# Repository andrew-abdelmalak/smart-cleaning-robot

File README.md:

# Smart Cleaning Robot

MicroPython firmware for a low-cost floor-cleaning robot built on a Raspberry Pi Pico W, with Bluetooth Low Energy (BLE) remote control, ultrasonic obstacle avoidance, and feed-forward plus PID wheel control. It was my bachelor thesis project at the German University in Cairo (GUC), 2025.

<p align="center">
  
  &nbsp;
  
</p>

The robot is a 35 cm round chassis that I designed in SolidWorks and 3D-printed, with a custom KiCad PCB and a repurposed PS3 fan for suction. In autonomous mode it drives straight until something is closer than 15 cm, then pivots left and carries on. From a phone you can drive it, toggle the fan, and sound a horn. The parts cost 3,950 EGP in 2025, about 80 USD at the time.

**[Try it in your browser](https://andrew-abdelmalak.github.io/smart-cleaning-robot/):** the project site runs this firmware, unchanged, in a drawn room you can drive it around, next to the real footage and the build story.

*The project in 34 seconds; select it for the version with sound. Music: “Happy Beats & Business Moves Vol. 10” by Sascha Ende ([ende.app](https://ende.app/en)), [CC BY 4.0](https://creativecommons.org/licenses/by/4.0/).*

## Results

From the prototype tests in the [thesis](https://andrew-abdelmalak.github.io/smart-cleaning-robot/pdfjs/web/viewer.html?file=../../thesis.pdf#page=1) (Table 4.2 and section 5.1.1):

| Metric | Result |
|---|---|
| Battery runtime | More than 60 minutes of continuous autonomous operation |
| BLE range | Stable indoor connection at more than 5 m |
| Straight-line driving | PID correction noticeably reduced drift compared with open loop |
| Stall recovery | Detected a stuck wheel and recovered in simulated stuck conditions |
| Cleaning | Collected light debris (paper, dust) from hard floors |
| System power | About 26 W at 12 V (estimate from component ratings) |
| Build cost | 3,950 EGP in parts (about 80 USD at the June 2025 exchange rate), against 100 to 900 USD for the commercial robots I compared |
| Size and weight | 35 cm diameter, 17 cm high, 2.65 kg |

## How it works

<picture>
  <source media="(prefers-color-scheme: dark)" srcset="docs/diagrams/architecture-dark.svg">
  
</picture>

The firmware is one file, [`firmware/main.py`](firmware/main.py), that runs a 20 ms control loop. Each pass handles, in priority order:

| Priority | Condition | Action |
|---|---|---|
| 1 | Horn on | Buzz the motors at 10% duty as an audible horn |
| 2 | Manual command active | Drive forward, backward, or pivot |
| 3 | Autonomous mode on | Advance the cleaning state machine one step |
| 4 | Otherwise | Make sure both motors are stopped |

### Autonomous cleaning

<picture>
  <source media="(prefers-color-scheme: dark)" srcset="docs/diagrams/state-machine-dark.svg">
  
</picture>

From IDLE, `CLEAN` starts forward driving. An obstacle closer than 15 cm triggers a 39-pulse left pivot. A wheel stall longer than 800 ms triggers a reverse, then the same pivot. Both return to forward driving.

### Motion control

A pure PID controller on the wheel encoders drew enough current to cause brownouts that stalled a motor. The final design uses a feed-forward motor model for most of the drive and keeps the PID only as a small correction to each wheel's target speed. The earlier versions on the way here, from timed driving to per-wheel PID and the tuner that found the final gains, are in [`docs/history/`](docs/history/).

<picture>
  <source media="(prefers-color-scheme: dark)" srcset="docs/diagrams/control-loop-dark.svg">
  
</picture>

| Loop | Purpose | P / I / D |
|---|---|---|
| Straight | Keep both wheels at the same distance travelled | 0.8 / 0.15 / 0.25 |
| Turn progress | Reach the target pivot of 39 encoder pulses | 0.6 / 0.1 / 0.2 |
| Turn balance | Share the pivot between both wheels | 1.5 / 0.05 / 0.3 |

The feed-forward model is `PWM = kS + kV × speed`, fitted per wheel (left: kS 27, kV 0.66; right: kS 30, kV 0.61), with a right-wheel trim of 0.75 and duty capped at 95%. All integrals are clamped to ±15.

## Hardware

| Part | Component | Pins (GP = Pico GPIO) |
|---|---|---|
| Controller | Raspberry Pi Pico W | |
| Motor driver | L298N dual H-bridge | ENA 6, ENB 7, IN1 to IN4 12 to 15 |
| Drive | 2 TT DC gear motors, 66 mm wheels | |
| Wheel encoders | 20-slot optical discs, one channel per wheel | Left 21, right 20 |
| Obstacle sensor | HC-SR04 ultrasonic | TRIG 10, ECHO 11 |
| Suction | PS3 Slim fan, 12 V, on/off through its PWM wire | 8 |
| Status LED | Green LED | 18 |
| Button | Push button to GND, internal pull-up | 16 |
| Power | 12 V Li-ion pack, LM2596S buck converter to 5 V | |
| Chassis and PCB | 3D-printed PLA+, custom KiCad PCB | |

The KiCad project for the board, the SolidWorks files for the printed parts, and their drawings are in [`hardware/`](hardware/). The thesis has the full bill of materials (Appendix A).

## Getting started

You need a Raspberry Pi Pico W with [MicroPython for the Pico W](https://micropython.org/download/RPI_PICO_W/) (the robot ran v1.25.0, from April 2025), [`mpremote`](https://docs.micropython.org/en/latest/reference/mpremote.html), and a phone with [nRF Toolbox](https://www.nordicsemi.com/Products/Development-tools/nrf-toolbox) or another BLE UART app.

1. Flash MicroPython: hold BOOTSEL while you connect USB, then copy the `.uf2` file to the drive that appears.
2. Copy the firmware to the board as `main.py`, so it runs at boot:

   ```bash
   mpremote cp firmware/main.py :main.py
   ```

3. Reset the board. It advertises as `PicoRobot-XXXX`, where `XXXX` comes from the board ID.
4. Connect from nRF Toolbox (UART) and send the commands below.

> [!WARNING]
> Test with the wheels off the ground first, and check the motor wiring before you enable autonomous mode. I tuned the gains and thresholds for this chassis; expect to retune `OBSTACLE_THRESHOLD_CM`, `TURN_PULSES`, and the PID gains for another build.

### Commands

Send these as text over the Nordic UART Service (writes go to RX characteristic `6E400002-B5A3-F393-E0A9-E50E24DCCA9E`). Case and surrounding spaces are ignored.

| Command | Effect |
|---|---|
| `FORWARD` | Drive straight with PID correction. Stops with the horn if an obstacle is closer than 15 cm |
| `BACKWARD`, `LEFT`, `RIGHT` | Drive backward, or pivot in place |
| Same command again | Brake and stop |
| `CLEAN` | From a full stop: toggle autonomous cleaning (fan on, state machine running). While moving: emergency stop |
| `FAN` | Toggle the suction fan (only while stopped) |
| `HORN` | Toggle the horn. Also silences the obstacle alarm |

The push button does the same as `CLEAN`. Losing the BLE connection stops the robot.

| Status LED | Meaning |
|---|---|
| Off | Idle, no phone connected |
| Slow flash | Phone connected |
| Solid | Autonomous cleaning |
| Rapid flash | Horn on or path blocked |

## Development

The tests run the real firmware on your computer against fake `machine`, `bluetooth`, and `time` modules, with a simulated clock that wraps like MicroPython's. They cover the motion math, the command handling, the safety stops, and the state machine. You need [uv](https://docs.astral.sh/uv/).

```bash
uv sync
uv run pytest
uv run ruff check .
uv run ruff format --check .
uv run mpy-cross -o main.mpy firmware/main.py
```

CI runs the same steps on every push and pull request.

The site serves its third-party browser code (MicroPython WebAssembly, transformers.js, and the ONNX runtime) itself. `package.json` lists the versions; nothing installs them. `scripts/vendor.json` pins each file by SHA-256, taken from the npm package tarball after checking the tarball against the registry. Dependabot proposes new versions in `package.json`, and CI then fails until the pins are refreshed on that branch:

```bash
python3 scripts/fetch_vendor.py --update
```

To preview the site locally, fetch the files into `site/vendor/` (ignored by git) and serve `site/`:

```bash
python3 scripts/fetch_vendor.py site/vendor
```

The Pages build also adds Mozilla's PDF.js viewer, pinned by version and SHA-256 in `.github/workflows/pages.yml`, so the thesis links open only on the deployed site.

The site's "Ask the thesis" search ranks passages from `site/thesis-index.json`. `scripts/thesis_latex.py` reads the passages from the thesis LaTeX, so results keep their headings, lists, tables, bold text, and subscripts. The build then places each passage on its PDF page and checks its words and numbers against the PDF's own text, so a parsing mistake stops the build. To rebuild the index after the thesis changes, install poppler's `pdftotext` and run:

```bash
uv sync --group search
uv run scripts/build_thesis_index.py
uv run pytest tests/test_thesis_index.py
```

With the `search` group installed, the tests also embed 21 sample questions and check that most find the section that answers them in the top three results. When I built the index, 17 of the 21 did. CI skips that check because it needs a 23 MB model download, but still checks that the index matches what the parser reads from the LaTeX.

```text
firmware/main.py      MicroPython firmware (copy to the board as main.py)
hardware/             KiCad board, SolidWorks parts, and drawings
scripts/              Builds the thesis search index; fetches the site's pinned libraries
tests/                Host-side tests and hardware fakes
docs/diagrams/        Diagrams used in this README
docs/history/         Earlier firmware versions, kept as written
docs/media/           Demo clips from the thesis presentation and the project video
docs/thesis/          Thesis PDF and its LaTeX source
site/                 Project site: the firmware in a drawn room, and thesis search
```

## Known limitations

These come from the hardware and the hand tuning, and need the robot to fix and verify:

- Navigation is reactive. The robot pivots left at every obstacle; it does not map the room or follow a coverage pattern.
- The turn-balance PID adds the two wheel counts rather than comparing them, because the single-channel encoders cannot tell direction. I tuned the gains with it working that way on the prototype.
- A disconnected ultrasonic sensor reads as a clear path. A missing echo returns 999 cm.
- Pivots have no timeout. A dead encoder during a turn keeps the robot spinning.
- Braking always pulses backward, whatever the direction of travel.
- BLE has no pairing, so any phone in range can connect and drive the robot.
- Cleaning: no check valve and no brushes, so debris can spill and embedded dirt stays.

## Thesis

*Design and Implementation of a Smart Cleaning Robot*, Andrew Khalil Samuel Abdelmalak, Faculty of Engineering and Materials Sciences, German University in Cairo, June 2025.

- [Thesis PDF](https://andrew-abdelmalak.github.io/smart-cleaning-robot/pdfjs/web/viewer.html?file=../../thesis.pdf#page=1)
- [LaTeX source](docs/thesis/main.tex), also on [Overleaf (read only)](https://www.overleaf.com/read/hzhdgbtyqgmt#95d41f)
- [Ask the thesis](https://andrew-abdelmalak.github.io/smart-cleaning-robot/#thesis): semantic search over the thesis on the project site, which links each result to its page in the PDF

The firmware has changed since the thesis: it now has tests, CI, and fixes for five control-logic bugs. See [CHANGELOG.md](CHANGELOG.md).

Supervised by Prof. Dr. Walid Atef Hafez Omran, co-supervised by Dr. Hisham Mostafa El Sherif, and reviewed by Dr. M. A. Moustafa Hassan.

## Contributing and security

This is a finished thesis project, so I do not plan new features. Bug reports and fixes are welcome; see [CONTRIBUTING.md](.github/CONTRIBUTING.md). Report security issues privately as described in [SECURITY.md](.github/SECURITY.md).

## License

Released under the [MIT License](LICENSE).

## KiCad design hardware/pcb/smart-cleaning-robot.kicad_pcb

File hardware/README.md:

# Hardware design files

The sources I made for the robot's custom parts: the circuit board in KiCad and the 3D-printed parts in SolidWorks, with their drawings. They are released under the same [MIT License](../LICENSE) as the rest of the repository. The thesis (chapters 3 and 4) explains the design choices.

## Circuit board

[`pcb/`](pcb/) is a KiCad 9 project: open `smart-cleaning-robot.kicad_pro` in [KiCad](https://www.kicad.org/) 9 or later, which is free. It is a two-layer board, 100 × 50 mm, that carries the Raspberry Pi Pico W, an LM2596 step-down module, three resistors (2.2 kΩ, 4.7 kΩ, 330 Ω), and screw terminals for the power input, the motor driver, the ultrasonic sensor, the fan, the start and stop buttons, and the LED. It has no terminals for the wheel encoders.

| Schematic | Layout | 3D view |
|---|---|---|
|  |  |  |

The symbols and footprints, including the Pico W and the LM2596 module from third-party KiCad libraries, are embedded in the project files. The Pico W's 3D model path still points to my own computer, so KiCad's 3D viewer shows the board without that one model.

## 3D-printed parts

[`cad/`](cad/) holds the SolidWorks 2024 part files, printed in PLA+. They open in SolidWorks 2024 or later, and the free eDrawings Viewer can display them. I renamed the files to say what each part is.

| Part | File | Drawing |
|---|---|---|
| Chassis: the round shell, 35 cm across | [`chassis.SLDPRT`](cad/chassis.SLDPRT) | [`chassis.pdf`](drawings/chassis.pdf) |
| Lid | [`lid.SLDPRT`](cad/lid.SLDPRT) | [`lid.pdf`](drawings/lid.pdf) |
| Debris collection chamber | [`debris-chamber.SLDPRT`](cad/debris-chamber.SLDPRT) | [`debris-chamber.pdf`](drawings/debris-chamber.pdf) |
| Plate with a 5 cm opening, matching the chamber's port | [`chamber-plate.SLDPRT`](cad/chamber-plate.SLDPRT) | [`chamber-plate.pdf`](drawings/chamber-plate.pdf) |
| Support blocks, small and large | [`support-small.SLDPRT`](cad/support-small.SLDPRT), [`support-large.SLDPRT`](cad/support-large.SLDPRT) | [`support-small.pdf`](drawings/support-small.pdf), [`support-large.pdf`](drawings/support-large.pdf) |
| Mounts | [`mount-1.SLDPRT`](cad/mount-1.SLDPRT), [`mount-2.SLDPRT`](cad/mount-2.SLDPRT) | none |

The full assembly is not included: it uses the motor, motor driver, sensor, and wheel models I downloaded from GrabCAD, which their authors share under their own terms.

The drawings were made with the SolidWorks Education Edition, which prints its watermark on each sheet. Their dimensions are in centimetres, although the title block's default note says millimetres.

| Assembled chassis | Open chassis |
|---|---|
|  |  |

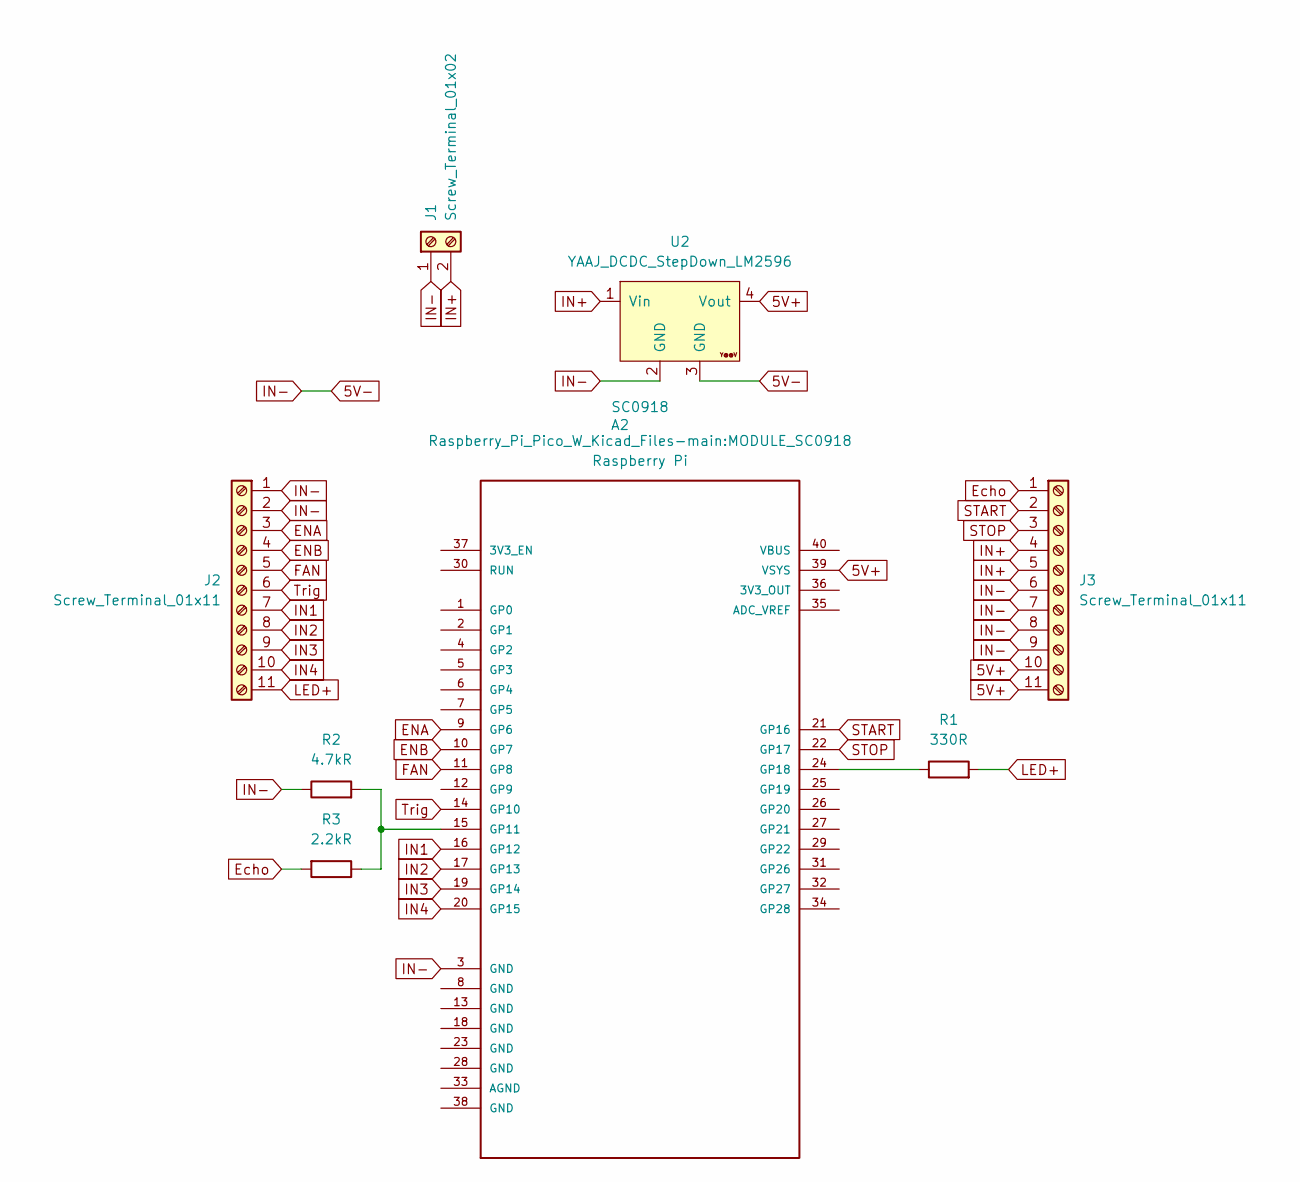
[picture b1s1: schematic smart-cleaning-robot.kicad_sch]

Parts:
A2: SC0918; MODULE_SC0918; PARTREV 1.6
J1: Screw_Terminal_01x02; TerminalBlock_MaiXu_MX126-5.0-02P_1x02_P5.00mm
J2, J3: Screw_Terminal_01x11; TerminalBlock_MaiXu_MX126-5.0-11P_1x11_P5.00mm
R1: 330R; R_Axial_DIN0207_L6.3mm_D2.5mm_P10.16mm_Horizontal
R2: 4.7kR; R_Axial_DIN0207_L6.3mm_D2.5mm_P10.16mm_Horizontal
R3: 2.2kR; R_Axial_DIN0207_L6.3mm_D2.5mm_P10.16mm_Horizontal
U2: YAAJ_DCDC_StepDown_LM2596

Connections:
5V+: A2.39 (VSYS), J3.10, J3.11, U2.4 (Vout)
5V-: A2.3 (GND), J1.1, J2.1, J2.2, J3.6, J3.7, J3.8, J3.9, R2.1, U2.2 (GND), U2.3 (GND)
ENA: A2.9 (GP6), J2.3
ENB: A2.10 (GP7), J2.4
Echo: J3.1, R3.2
FAN: A2.11 (GP8), J2.5
IN1: A2.16 (GP12), J2.7
IN2: A2.17 (GP13), J2.8
IN3: A2.19 (GP14), J2.9
IN4: A2.20 (GP15), J2.10
IN+: J1.2, J3.4, J3.5, U2.1 (Vin)
LED+: J2.11, R1.2
unnamed: A2.15 (GP11), R2.2, R3.1
unnamed: A2.24 (GP18), R1.1
START: A2.21 (GP16), J3.2
STOP: A2.22 (GP17), J3.3
Trig: A2.14 (GP10), J2.6

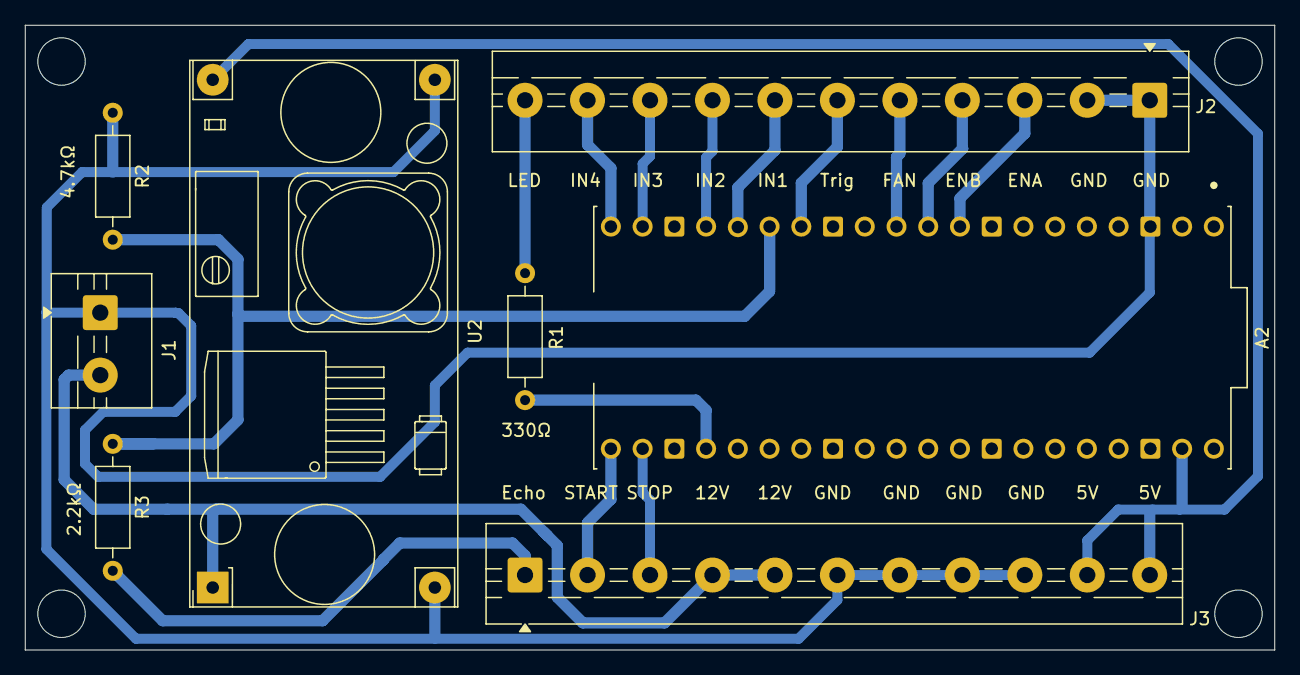
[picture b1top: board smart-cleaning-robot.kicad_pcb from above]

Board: 2 copper layers, 100.0 x 50.0 mm, 8 parts (0 on the bottom side), 17 nets.

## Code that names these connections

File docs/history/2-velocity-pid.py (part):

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# =====================================================================================

# Motor Control Pins
ENA_PIN, IN1_PIN, IN2_PIN = 6, 12, 13
ENB_PIN, IN3_PIN, IN4_PIN = 7, 14, 15

# Encoder Input Pins
PHYSICAL_LEFT_ENCODER_PIN = 21
PHYSICAL_RIGHT_ENCODER_PIN = 20

# Peripheral Device Pins
FAN_PIN = 8
LED_WORK_PIN = 18
TRIG_PIN = 10
ECHO_PIN = 11
BUTTON_PIN_NUMBER = 16

# =====================================================================================
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# =====================================================================================

# Initialize Motor PWM Controllers
ena = PWM(Pin(ENA_PIN))
enb = PWM(Pin(ENB_PIN))
ena.freq(1000)
enb.freq(1000)

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right_enc_pin = Pin(PHYSICAL_RIGHT_ENCODER_PIN, Pin.IN, Pin.PULL_UP)

# Initialize Peripheral Device Pins
fan = Pin(FAN_PIN, Pin.OUT)
led = Pin(LED_WORK_PIN, Pin.OUT)
trig = Pin(TRIG_PIN, Pin.OUT)
echo = Pin(ECHO_PIN, Pin.IN)
button = Pin(BUTTON_PIN_NUMBER, Pin.IN, Pin.PULL_UP)

# =====================================================================================
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
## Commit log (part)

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2026-03-19 Polish repo for publication
    - Overhaul README with full thesis data: overview table, hardware
    specifications, pin-mapping, BLE command reference (GATT UUIDs +
    command table), key-results table, cost-comparison table (60-90 %
    cheaper than commercial platforms), autonomous FSM state table,
    PID/feed-forward control-design section, author + supervisors table,
    acknowledgments, and thesis citation
2026-03-19 Standardize repository structure: Expand .gitignore to 7-section standard format
    - Reorganize .gitignore from 4 sections (21 lines) to 7-section standard
    format: OS / IDE / Python / MicroPython / Logs / Archives
    - Adds MicroPython-specific entries (.mpy, boot_out.txt, .micropython/,
    flash/) and broader archive coverage (.zip, .tar.gz, .rar, .7z)
    - Aligns with standardization plan across all repositories
2026-03-19 Fix Phase 2 audit: add References section, standardize .gitignore headers
    - README.md: add ## References section (6 citations: Choset coverage
    robotics, Cadena SLAM, Durrant-Whyte SLAM, Raspberry Pi Pico W
    datasheet, L298N datasheet, HC-SR04 datasheet) — inserted before
    ## License to complete the standard section sequence
    - .gitignore: convert section headers from # ── format to
    # ======================== standard used across all other repositories;

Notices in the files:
README.md:
License: MIT
